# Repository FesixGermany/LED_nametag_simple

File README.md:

# LED nametag  

 Since many attendees are wearing some blinky LED stuff at the Chaos Communication Congress I wanted to also make myself an eye catcher  and present a little project. It was also a good opportunity to make a proper two layer PCB again to get more practice. The goal was to have the project finished or at least functional for 38C3. Since I got asked by attendees about the tag I decided to make this documentation.
 
The result is a little PCB to be worn e.g. on a collar with the outline shaped like a bone with LEDs arranged so it spells my name.
The electronics basically consists of the following:
- TP4056 lithium charger IC for a 100mAh LiPo battery
- MPM3810 DCDC converter to lower the voltage so all LEDs can be operated in parallel without a resistor
- ATtiny24 microcontroller giving PWM to the MOSFETs that switch the individual letters and the LEDs on the back
- [Paw-connect by LeoDJ](https://github.com/LeoDJ/Paw-Connect) as the ISP interface and as another eye catching feature
- Place for a photodiode to be able to adjust the brightness of the LEDs automatically depending on the surrounding

One tricky thing was to find the right voltage for the DCDC converter output so the LEDs are not too dimm at maximum brightness and not too bright as the duty cycle of the PWM would have to be extremely small on lower brightness settings and therefore one would loose the resolution for the animations.

The firmware only got to a point where I had a single simple animation running without the integration of the mentioned photodiode. That would probably require the code to be made more efficient as the memory of the controller already is quite full.

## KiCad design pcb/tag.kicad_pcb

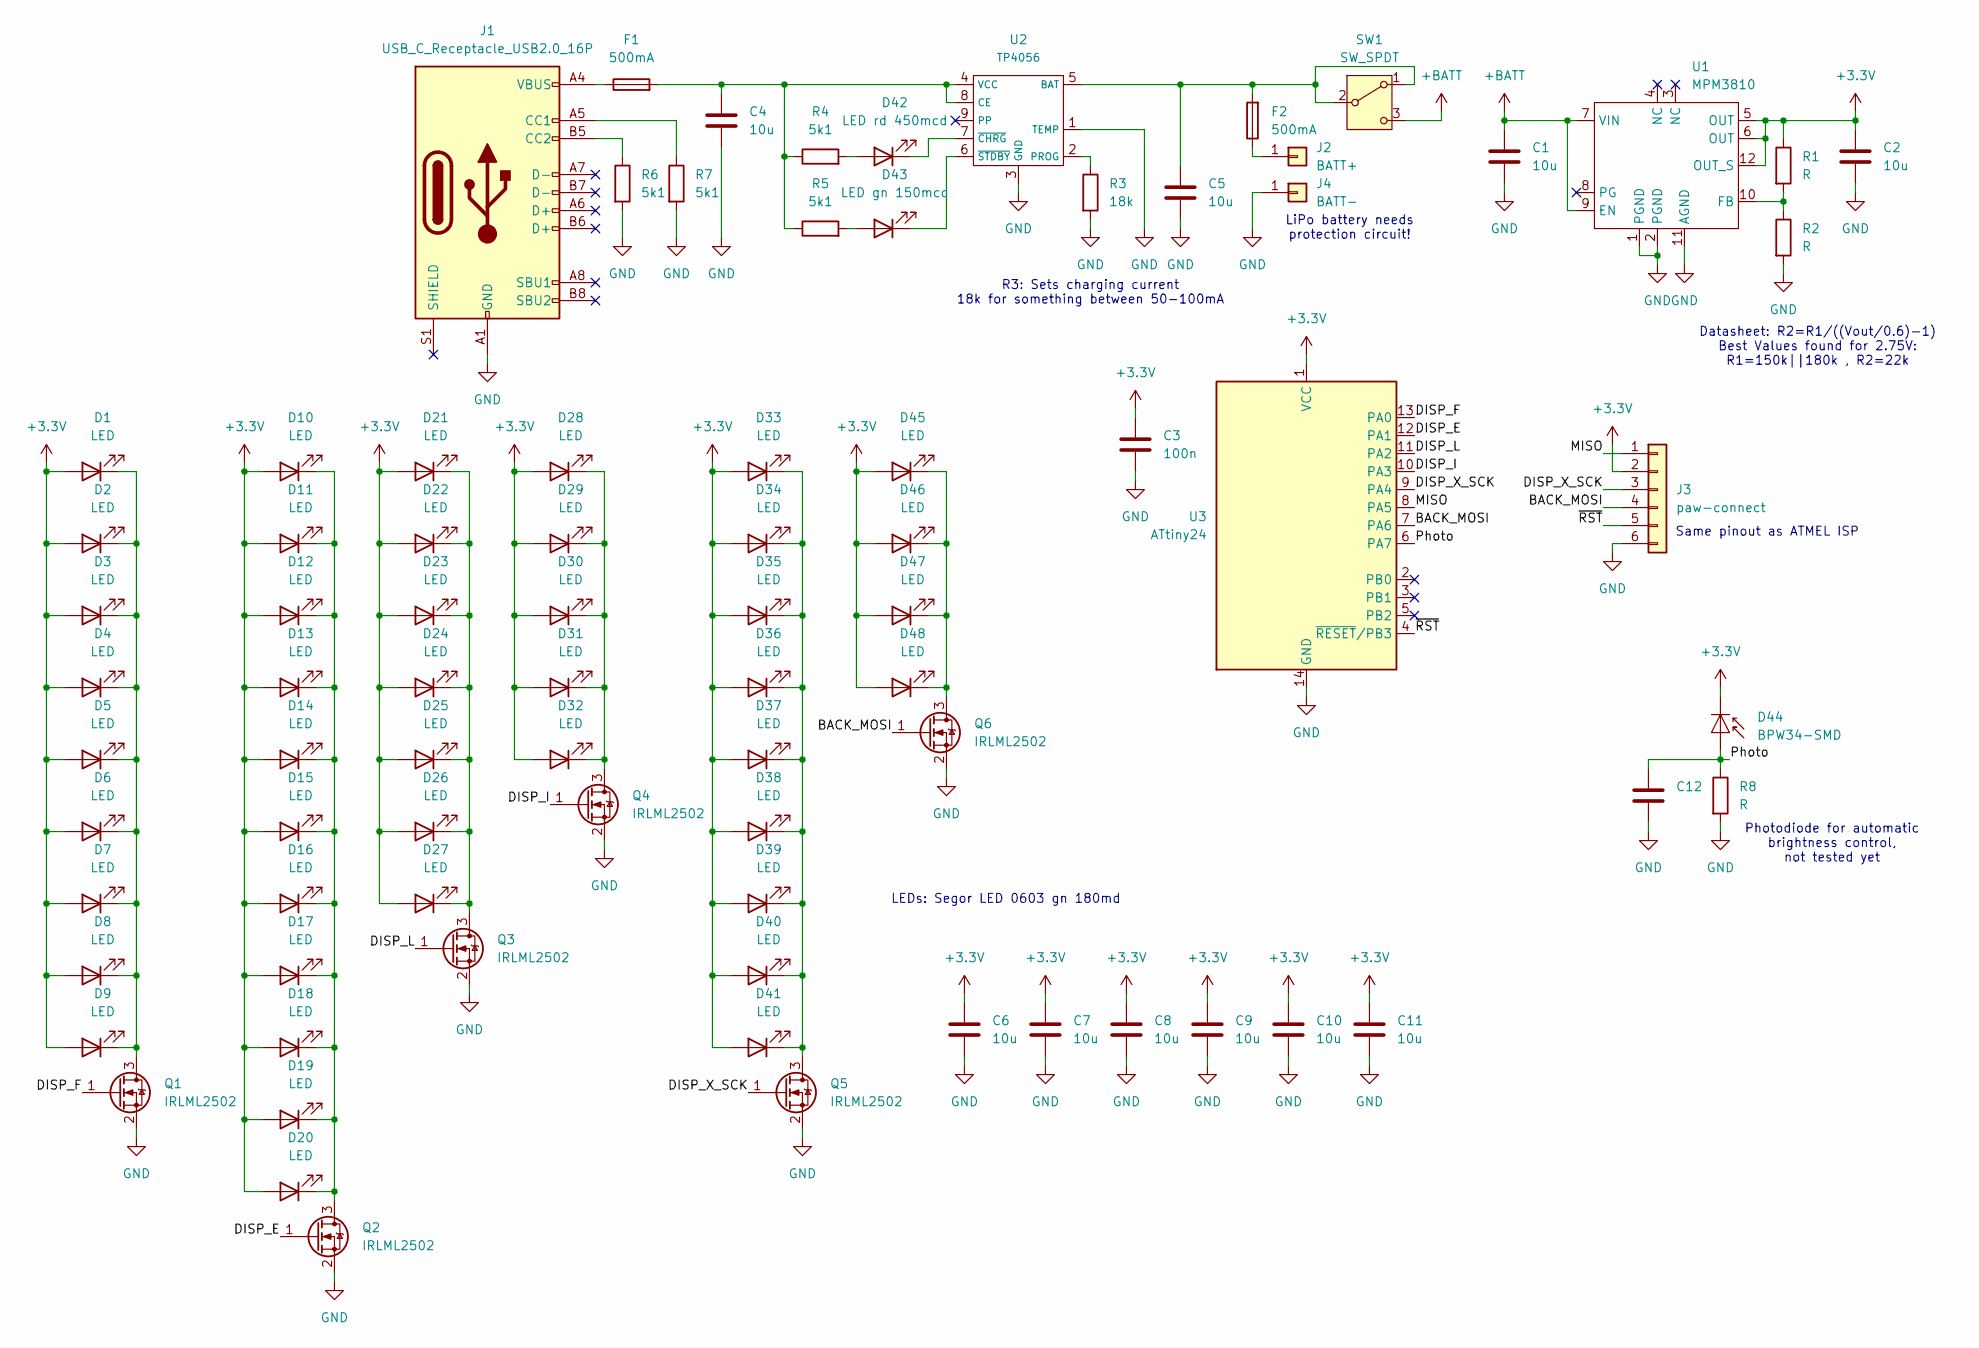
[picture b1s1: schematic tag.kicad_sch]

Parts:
C1, C2, C4, C5, C6, C7, C8, C9, C10, C11: 10u; C_0603_1608Metric
C3: 100n; C_0603_1608Metric
C12: C_0603_1608Metric
D1, D2, D3, D4, D5, D6, D7, D8, D9, D10, D11, D12, D13, D14, D15, D16, D17, D18, D19, D20, D21, D22, D23, D24, D25, D26, D27, D28, D29, D30, D31, D32, D33, D34, D35, D36, D37, D38, D39, D40, D41, D45, D46, D47, D48: LED; LED_0603_1608Metric
D42: LED rd 450mcd; LED_0603_1608Metric
D43: LED gn 150mcd; LED_0603_1608Metric
D44: BPW34-SMD; Osram_BPW34S-SMD
F1, F2: 500mA; Fuse_0603_1608Metric_Pad1.05x0.95mm_HandSolder
J1: USB_C_Receptacle_USB2.0_16P; USB_C_Receptacle_G-Switch_GT-USB-7010ASV
J2: BATT+; SolderWirePad_1x01_SMD_1x2mm
J3: paw-connect; Paw-Connect_RevA_TC2030-IDC-NL_2x03_P1.27mm_Vertical
J4: BATT-; SolderWirePad_1x01_SMD_1x2mm
Q1, Q2, Q3, Q4, Q5, Q6: IRLML2502; SOT-23
R1, R2, R8: R; R_0603_1608Metric
R3: 18k; R_0603_1608Metric
R4, R5, R6, R7: 5k1; R_0603_1608Metric
SW1: SW_SPDT; SW_SPDT_PCM12
U1: MPM3810
U2: TP4056; SOIC-8-1EP_3.9x4.9mm_P1.27mm_EP2.29x3mm
U3: ATtiny24; SOIC-14_3.9x8.7mm_P1.27mm

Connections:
+3.3V: C2.1, C3.1, C6.1, C7.1, C8.1, C9.1, C10.1, C11.1, D1.2 (A), D2.2 (A), D3.2 (A), D4.2 (A), D5.2 (A), D6.2 (A), D7.2 (A), D8.2 (A), D9.2 (A), D10.2 (A), D11.2 (A), D12.2 (A), D13.2 (A), D14.2 (A), D15.2 (A), D16.2 (A), D17.2 (A), D18.2 (A), D19.2 (A), D20.2 (A), D21.2 (A), D22.2 (A), D23.2 (A), D24.2 (A), D25.2 (A), D26.2 (A), D27.2 (A), D28.2 (A), D29.2 (A), D30.2 (A), D31.2 (A), D32.2 (A), D33.2 (A), D34.2 (A), D35.2 (A), D36.2 (A), D37.2 (A), D38.2 (A), D39.2 (A), D40.2 (A), D41.2 (A), D44.1 (K), D45.2 (A), D46.2 (A), D47.2 (A), D48.2 (A), J3.2, R1.1, U1.5 (OUT), U1.6 (OUT), U1.12 (OUT_S), U3.1 (VCC)
+BATT: C1.1, SW1.3 (C), U1.7 (VIN), U1.9 (EN)
/BACK_MOSI: J3.4, Q6.1 (G), U3.7 (PA6)
/DISP_E: Q2.1 (G), U3.12 (PA1)
/DISP_F: Q1.1 (G), U3.13 (PA0)
/DISP_I: Q4.1 (G), U3.10 (PA3)
/DISP_L: Q3.1 (G), U3.11 (PA2)
/DISP_X_SCK: J3.3, Q5.1 (G), U3.9 (PA4)
/MISO: J3.1, U3.8 (PA5)
/Photo: C12.1, D44.2 (A), R8.1, U3.6 (PA7)
/~RST: J3.5, U3.4 (~RESET/PB3)
GND: C1.2, C2.2, C3.2, C4.2, C5.2, C6.2, C7.2, C8.2, C9.2, C10.2, C11.2, C12.2, J1.A1 (GND), J1.A12 (GND), J1.B1 (GND), J1.B12 (GND), J3.6, J4.1, Q1.2 (S), Q2.2 (S), Q3.2 (S), Q4.2 (S), Q5.2 (S), Q6.2 (S), R2.2, R3.2, R6.2, R7.2, R8.2, U1.1 (PGND), U1.2 (PGND), U1.11 (AGND), U2.1 (TEMP), U2.3 (GND), U3.14 (GND)
unnamed: D1.1 (K), D2.1 (K), D3.1 (K), D4.1 (K), D5.1 (K), D6.1 (K), D7.1 (K), D8.1 (K), D9.1 (K), Q1.3 (D)
unnamed: D10.1 (K), D11.1 (K), D12.1 (K), D13.1 (K), D14.1 (K), D15.1 (K), D16.1 (K), D17.1 (K), D18.1 (K), D19.1 (K), D20.1 (K), Q2.3 (D)
unnamed: D21.1 (K), D22.1 (K), D23.1 (K), D24.1 (K), D25.1 (K), D26.1 (K), D27.1 (K), Q3.3 (D)
unnamed: D28.1 (K), D29.1 (K), D30.1 (K), D31.1 (K), D32.1 (K), Q4.3 (D)
unnamed: D33.1 (K), D34.1 (K), D35.1 (K), D36.1 (K), D37.1 (K), D38.1 (K), D39.1 (K), D40.1 (K), D41.1 (K), Q5.3 (D)
unnamed: D42.2 (A), R4.2
unnamed: D42.1 (K), U2.7 (~CHRG)
unnamed: D43.2 (A), R5.2
unnamed: D43.1 (K), U2.6 (~STDBY)
unnamed: D45.1 (K), D46.1 (K), D47.1 (K), D48.1 (K), Q6.3 (D)
unnamed: F1.1, J1.A4 (VBUS), J1.A9 (VBUS), J1.B4 (VBUS), J1.B9 (VBUS)
unnamed: J1.A5 (CC1), R7.1
unnamed: J1.B5 (CC2), R6.1
unnamed: F2.1, J2.1
unnamed: C5.1, F2.2, SW1.1 (A), SW1.2 (B), U2.5 (BAT)
unnamed: R1.2, R2.1, U1.10 (FB)
unnamed: C4.1, F1.2, R4.1, R5.1, U2.4 (VCC), U2.8 (CE)
unnamed: R3.1, U2.2 (PROG)

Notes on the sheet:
LiPo battery needs protection circuit!
Same pinout as ATMEL ISP
R3: Sets charging current 18k for something between 50-100mA
Datasheet: R2=R1/((Vout/0.6)-1) Best Values found for 2.75V: R1=150k||180k , R2=22k
LEDs: Segor LED 0603 gn 180md
Photodiode for automatic brightness control, not tested yet

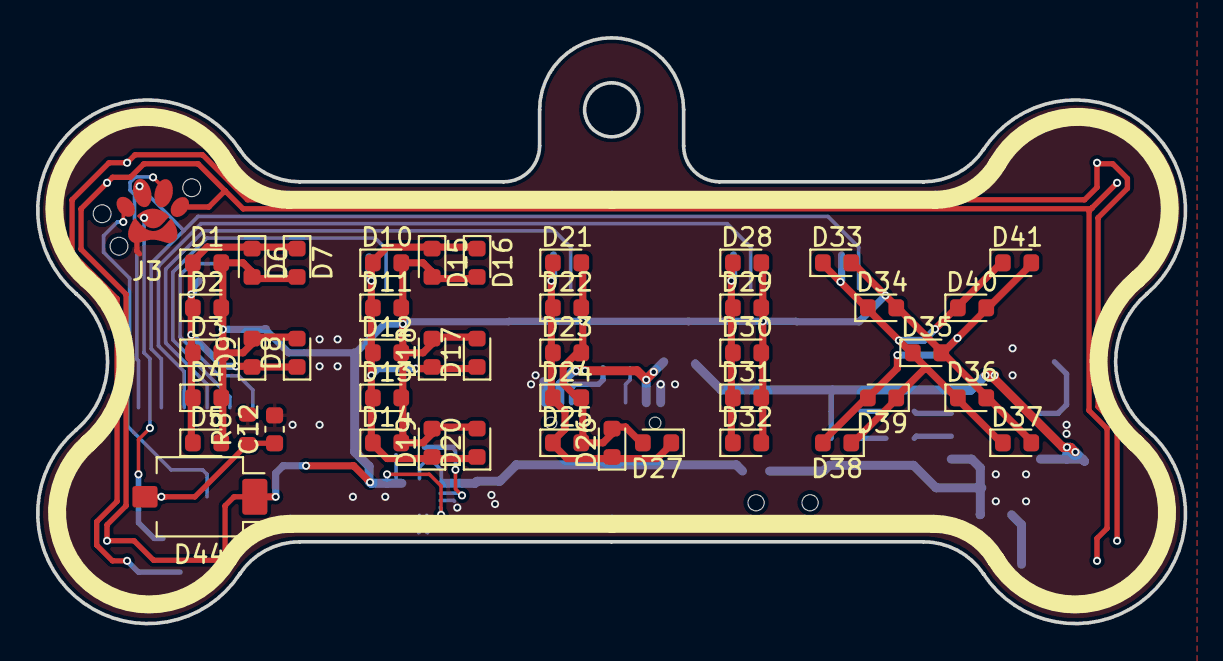
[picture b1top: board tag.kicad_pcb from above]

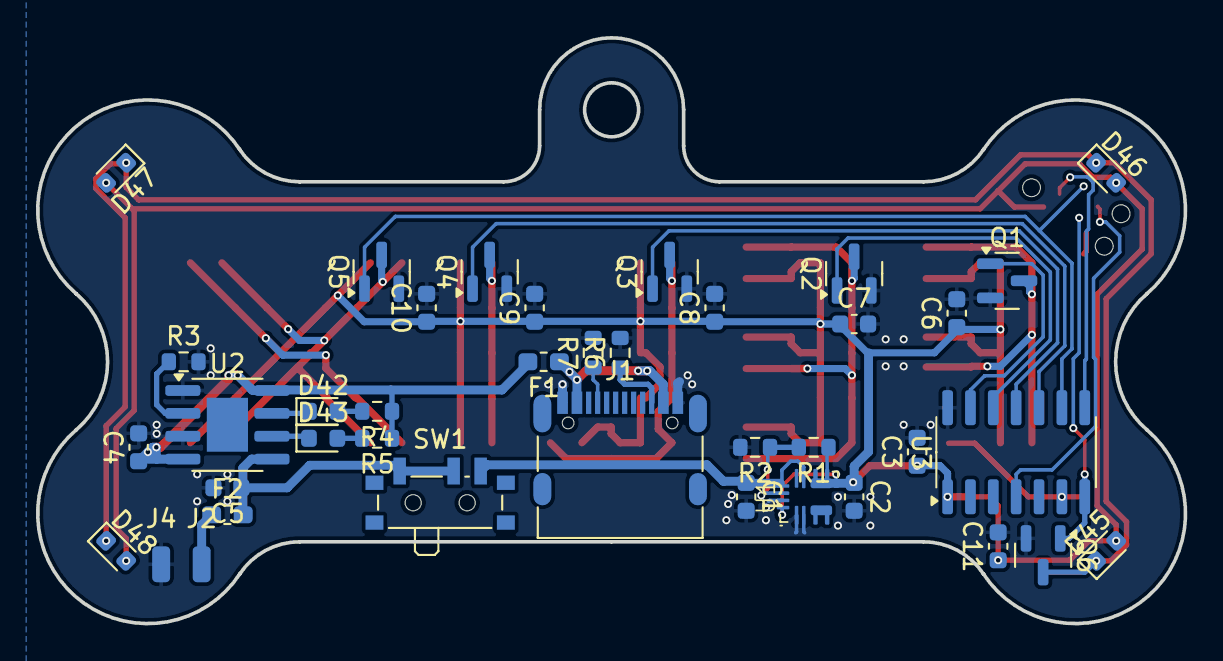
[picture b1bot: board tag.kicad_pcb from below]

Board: 2 copper layers, 63.8 x 32.5 mm, 84 parts (39 on the bottom side), 30 nets.

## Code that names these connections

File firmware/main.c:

/*
 * tag_firmware.c
 *
 * Created: 06/12/2024 15:24:56
 * Author : felix
 */ 

#include <avr/io.h>
#include <avr/interrupt.h>

// Internal 8MHz osc without CKDIV8
#define F_CPU		8000000UL

// Outputs
#define DISP_F		0
#define DISP_E		1
#define DISP_L		2
#define DISP_I		3
#define DISP_X		4
#define LED_BACK	6

// Inputs
#define PHOTODIODE	PA7

uint8_t pwmval_F=0;
uint8_t pwmval_E=0;
uint8_t pwmval_L=0;
uint8_t pwmval_I=0;
uint8_t pwmval_X=0;
uint8_t pwmval_BACK=0;

uint8_t pwmval_F_corr=0;
uint8_t pwmval_E_corr=0;
uint8_t pwmval_L_corr=0;
uint8_t pwmval_I_corr=0;
uint8_t pwmval_X_corr=0;
uint8_t pwmval_BACK_corr=0;

float light_prescaler = 0.2;
uint8_t displaybit = 0b00000000;							// Bits corresponding to PORTA bits
volatile unsigned long tick_animation = 0;					// long is 32 bits (4.29 billion), long long is 64 bits
volatile uint8_t tick_pwm = 0;
unsigned long animation_step = 0;
unsigned long old_step = 0;


void ADC_init(void)
{
	uint16_t result;
	
	// Default VCC as reference
	//ADMUX |= (1 << REFS1) | (1 << REFS0);					// 1.1V internal reference
	
	ADCSRA = (1 << ADPS2) | (1 << ADPS1);					// 64 ADC clock prescaler
	ADCSRA |= (1 << ADEN);									// ADC enable
	
	//Dummy-Readout
	ADCSRA |= (1 << ADSC);									// ADC single conversion
	while (ADCSRA & (1 << ADSC)) {}							// Wait until conversion is finished
	
	result = ADCW;											// Read register of result and do nothing with it
}

uint16_t ADC_Read(uint8_t channel)
{
	ADMUX = (ADMUX & ~(0x1F)) | (channel & 0x1F);			// Select ADC channel without interfering with other bits in register
	ADCSRA |= (1 << ADSC);									// ADC single conversion
	while (ADCSRA & (1 << ADSC)) {}							// Wait until conversion is finished
	
	return ADCW;											// Return value
}


void animation_fillup(void)
{
	// Scale the "animation_step" from tick_animation
	// e.g. one step every 200 interrupts
	animation_step = tick_animation / 200;		// divide by 200 equals 4ms per step
	
	if (animation_step != old_step)
	{
		old_step = animation_step;

		// Each phase is 256 steps: 0..255, 256..511, etc.
		if (animation_step < 256) {
			// Phase 0
			pwmval_F   = (uint8_t)animation_step;
			pwmval_E   = 0;
			pwmval_L   = 0;
			pwmval_I   = 0;
			pwmval_X   = 0;
		}
		else if (animation_step < 512) {
			// Phase 1
			uint16_t phase = animation_step - 256;
			pwmval_F = 255;
			pwmval_E = phase;
			pwmval_L = 0;
			pwmval_I = 0;
			pwmval_X = 0;
		}
		else if (animation_step < 768) {
			// Phase 2
			uint16_t phase = animation_step - 512;
			pwmval_F = 255;
			pwmval_E = 255;
			pwmval_L = phase;
			pwmval_I = 0;
			pwmval_X = 0;
		}
		else if (animation_step < 1024) {
			// Phase 3
			uint16_t phase = animation_step - 768;
			pwmval_F = 255;
			pwmval_E = 255;
			pwmval_L = 255;
			pwmval_I = phase;
			pwmval_X = 0;
		}
		else if (animation_step < 1280) {
			// Phase 4
			uint16_t phase = animation_step - 1024;
			pwmval_F = 255;
			pwmval_E = 255;
			pwmval_L = 255;
			pwmval_I = 255;
			pwmval_X = phase;
		}
		else if (animation_step < 1536) {
			// Phase 5
			uint16_t phase = animation_step - 1280;
			pwmval_F = 255 - phase;
			pwmval_E = 255;
			pwmval_L = 255;
			pwmval_I = 255;
			pwmval_X = 255;
		}
		else if (animation_step < 1792) {
			// Phase 6
			uint16_t phase = animation_step - 1536;
			pwmval_F = 0;
			pwmval_E = 255 - phase;
			pwmval_L = 255;
			pwmval_I = 255;
			pwmval_X = 255;
		}
		else if (animation_step < 2048) {
			// Phase 7
			uint16_t phase = animation_step - 1792;
			pwmval_F = 0;
			pwmval_E = 0;
			pwmval_L = 255 - phase;
			pwmval_I = 255;
			pwmval_X = 255;
		}
		else if (animation_step < 2304) {
			// Phase 8
			uint16_t phase = animation_step - 2048;
			pwmval_F = 0;
			pwmval_E = 0;
			pwmval_L = 0;
			pwmval_I = 255 - phase;
			pwmval_X = 255;
		}
		else if (animation_step < 2560) {
			// Phase 9
			uint16_t phase = animation_step - 2304;
			pwmval_F = 0;
			pwmval_E = 0;
			pwmval_L = 0;
			pwmval_I = 0;
			pwmval_X = 255 - phase;
		}

		// Reset counter at end of animation
		if (animation_step >= 2560) {
			tick_animation = 0;
		}
	}
}

int main(void)
{
    // Outputs
	DDRA |= (1 << DISP_F) | (1 << DISP_E) | (1 << DISP_L) | (1 << DISP_I) | (1 << DISP_X) | (1 << LED_BACK);
	
	// Timer1 setup
	TCCR1B |= (1 << WGM12);						// CTC mode
	TCCR1B |= (1 << CS10);						// Prescaler 1
	OCR1A = 100;								// Top value
	TIMSK1 |= (1 << OCIE1A);					// Timer1 A interrupt enable
	
	sei();										// Enable interrupts globally
	
    while (1) 
    {
		animation_fillup();
		pwmval_BACK = 255;
		
		// Apply correction factor for maximum brightnes
		pwmval_F_corr = (int) (pwmval_F * light_prescaler);
		pwmval_E_corr = (int) (pwmval_E * light_prescaler);
		pwmval_L_corr = (int) (pwmval_L * light_prescaler);
		pwmval_I_corr = (int) (pwmval_I * light_prescaler);
		pwmval_X_corr = (int) (pwmval_X * light_prescaler);
		pwmval_BACK_corr = (int) (pwmval_BACK * light_prescaler);
	}
}


ISR (TIM1_COMPA_vect)
{		
	displaybit = 0x00;

	// Step 2: For each output, compare tick_pwm with its pwmval:
	if (tick_pwm < pwmval_F_corr)    displaybit |= (1 << DISP_F);
	if (tick_pwm < pwmval_E_corr)    displaybit |= (1 << DISP_E);
	if (tick_pwm < pwmval_L_corr)    displaybit |= (1 << DISP_L);
	if (tick_pwm < pwmval_I_corr)    displaybit |= (1 << DISP_I);
	if (tick_pwm < pwmval_X_corr)    displaybit |= (1 << DISP_X);
	if (tick_pwm < pwmval_BACK_corr) displaybit |= (1 << LED_BACK);

	// Set ports to high
	PORTA = displaybit;

	// Increment counters and reset if necessary
	tick_animation++;
	tick_pwm++;
	if (tick_pwm >= 255) tick_pwm = 0;
}

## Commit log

2024-12-30 clean doc
2024-12-30 link to paw-connect added
